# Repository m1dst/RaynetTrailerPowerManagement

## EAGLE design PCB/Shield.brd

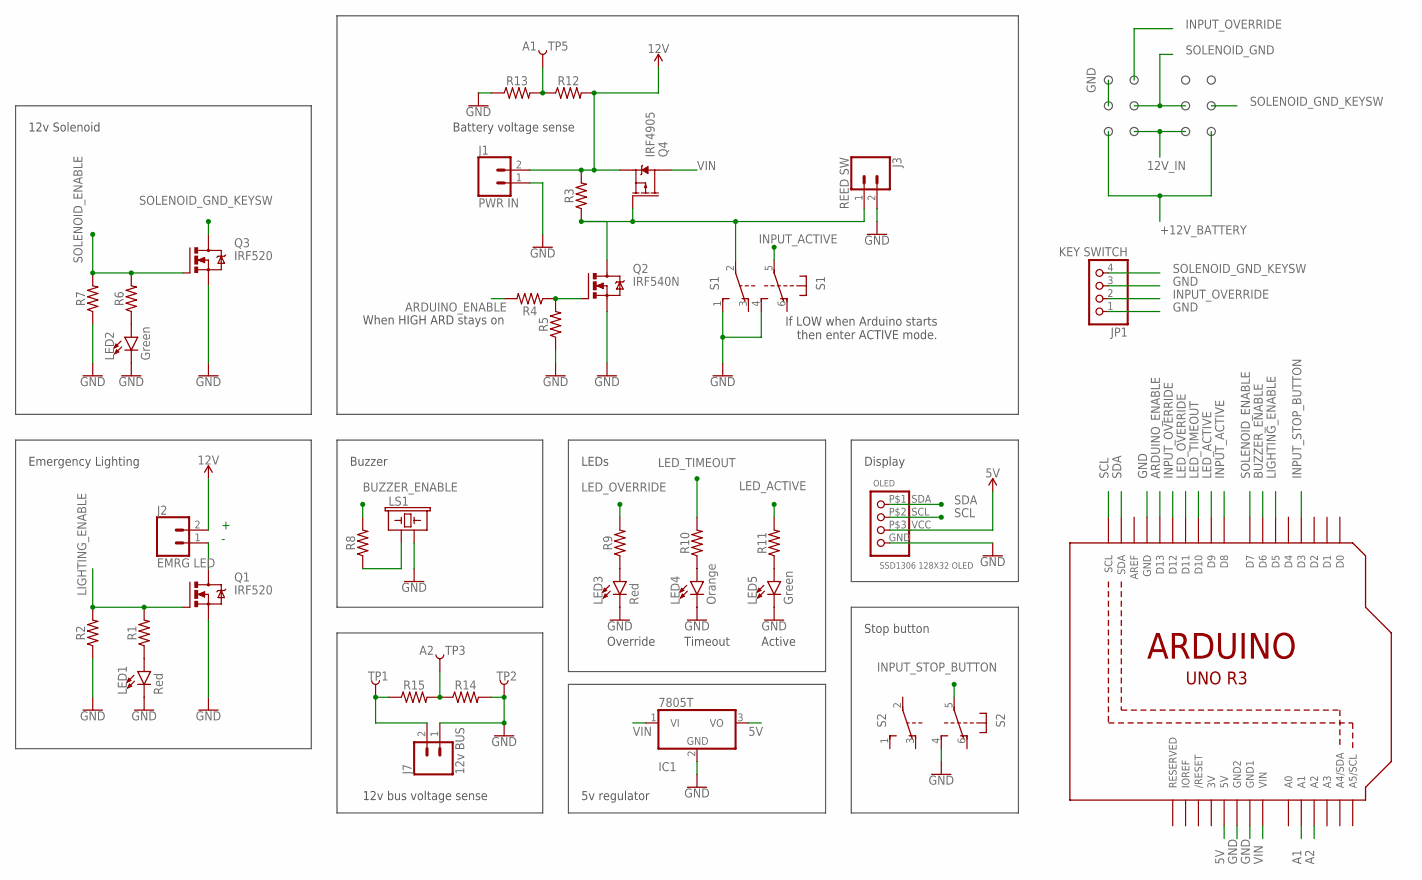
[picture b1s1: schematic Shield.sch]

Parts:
IC1: 7805T; TO220H
J1: PWR IN; SCREWTERMINAL-5MM-2
J2: EMRG LED; SCREWTERMINAL-5MM-2
J3: REED SW; SCREWTERMINAL-5MM-2
J7: 12v BUS; SCREWTERMINAL-5MM-2
JP1: KEY SWITCH; 1X04
LED1, LED3: Red; LED_3MM
LED2, LED5: Green; LED_3MM
LED4: Orange; LED_3MM
LS1: BUZZER; BUZZER-12MM-KIT
OLED: SSD1306 128X32 OLED; SSD1306_128X32_OLED
Q1, Q3: IRF520; TO220BV
Q2: IRF540N; TO220BV
Q4: IRF4905; TO220V
R1, R2, R6, R7: 1k; AXIAL-0.3
R3, R13, R14: 100k; AXIAL-0.3
R4, R8: 100; AXIAL-0.3
R5: 10k; AXIAL-0.3
R9, R10, R11: 330; AXIAL-0.3
R12, R15: 1m; AXIAL-0.3
S1, S2: 8X8_PCB_PUSH_BUTTON_DPDT
TP1, TP2, TP3, TP5: TEST-POINT3X5; PAD.03X.05
U1: ARDUINOR3-DIMENSION; ARDUINOR3

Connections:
3V: U1.3V
5V: IC1.3 (VO), OLED.P$3_VCC (VCC), U1.5V
12V_IN: J1.2, J2.2, Q4.3 (S), R3.P$2 (2), R12.P$2 (2)
A1: R12.P$1 (1), R13.P$2 (2), TP5.P$1, U1.A1
A2: R14.P$1 (1), R15.P$2 (2), TP3.P$1, U1.A2
ARDUINO_ENABLE: R4.P$2 (2), U1.D13
BUZZER_ENABLE: R8.P$2 (2), U1.D6
GND: IC1.2 (GND), J1.1, J3.2, J7.1, JP1.1, JP1.3, LED1.K (C), LED2.K (C), LED3.K (C), LED4.K (C), LED5.K (C), LS1.- (2), OLED.GND, Q1.S, Q2.S, Q3.S, R2.P$1 (1), R5.P$1 (1), R7.P$1 (1), R13.P$1 (1), R14.P$2 (2), S1.1 (S), S1.4 (S), S2.4 (S), TP2.P$1, U1.GND, U1.GND1, U1.GND2
INPUT_ACTIVE: S1.5, U1.D8
INPUT_OVERRIDE: JP1.2, U1.D12
INPUT_STOP_BUTTON: S2.5, U1.D3
LED_ACTIVE: R11.P$2 (2), U1.D9
LED_OVERRIDE: R9.P$2 (2), U1.D11
LED_TIMEOUT: R10.P$2 (2), U1.D10
LIGHTING_ENABLE: Q1.G, R1.P$2 (2), R2.P$2 (2), U1.D5
unnamed: J2.1, Q1.D
unnamed: LED1.A, R1.P$1 (1)
unnamed: J7.2, R15.P$1 (1), TP1.P$1
unnamed: J3.1, Q2.D, Q4.1 (G), R3.P$1 (1), S1.2
unnamed: Q2.G, R4.P$1 (1), R5.P$2 (2)
unnamed: LED2.A, R6.P$1 (1)
unnamed: LS1.+ (1), R8.P$1 (1)
unnamed: LED3.A, R9.P$1 (1)
unnamed: LED4.A, R10.P$1 (1)
unnamed: LED5.A, R11.P$1 (1)
SCL: OLED.P$2_SCL (SCL), U1.SCL
SDA: OLED.P$1_SDA (SDA), U1.SDA
SOLENOID_ENABLE: Q3.G, R6.P$2 (2), R7.P$2 (2), U1.D7
SOLENOID_GND_KEYSW: JP1.4, Q3.D
VIN: IC1.1 (VI), Q4.2 (D), U1.VIN

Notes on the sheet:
+ -
When HIGH ARD stays on
If LOW when Arduino starts then enter ACTIVE mode.
Emergency Lighting
12v Solenoid
Buzzer
Override
Timeout
Active
Battery voltage sense
12v bus voltage sense
LEDs
Display
Stop button
5v regulator

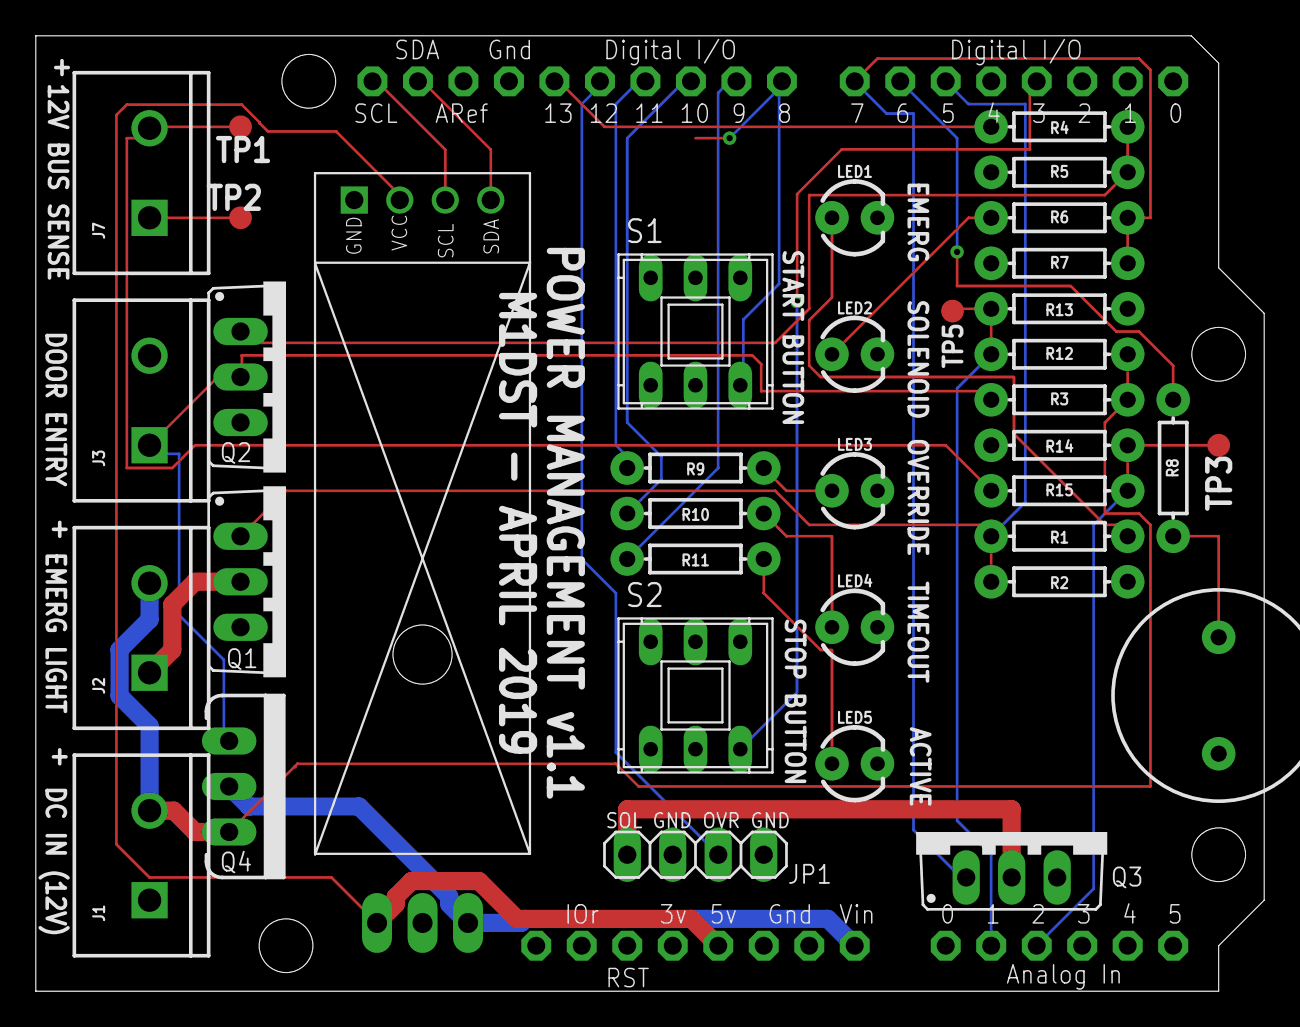
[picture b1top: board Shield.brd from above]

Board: 2 copper layers, 68.6 x 53.3 mm, 39 parts (1 on the bottom side), 29 nets.

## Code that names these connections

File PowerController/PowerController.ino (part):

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
#define SPARE               2     // Currently unused.
#define SOUND_BOMB          3     // The external burglar alarm
#define LIGHTING_ENABLE     4     // Emergency lighting.
#define SPARE_PWM           5     // Currently unused.
#define BUZZER_ENABLE       6     // The small buzzer.
#define SOLENOID_ENABLE     7     // The solenoid enable line.
#define INPUT_ACTIVE        8     // The start button
#define LED_ACTIVE          9     // Indicates if the Arduino power is now latched.
#define LED_TIMEOUT         10    // Indicates if the unit is in timeout mode and will eventually shutdown if no interaction occurs.
#define LED_OVERRIDE        11    // Indicates if override is active.
#define INPUT_OVERRIDE      12    // If grounded (via the keyswitch) the startup and under/over voltage checks are ignored.
#define ARDUINO_ENABLE      13    // Keeps the Arduino running.  If this pin goes low the Arduino will power off.

#define INPUT_ALARM_DISABLE A0    // Button to disable the alarm
#define INPUT_BATTERY_SENSE A1    // Measures the voltage of the battery.
#define INPUT_BUS_SENSE     A2    // Measures the voltage of the bus (controlled by the solenoid)
#define INPUT_STOP_BUTTON   A3    // The stop button.

#define BUZZER_SUPPORTED          // If uncommented, the buzzer will sound during events such as timeout.  Disabled during development.
#define DISPLAY_SUPPORTED         // If uncommented, the buzzer will sound during events such as timeout.  Disabled during development.
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  Serial.begin(115200);
  Serial.println("Starting...");

  pinMode(INPUT_STOP_BUTTON, INPUT);
  pinMode(INPUT_ACTIVE, INPUT_PULLUP);
  pinMode(INPUT_OVERRIDE, INPUT_PULLUP);

  pinMode(SOUND_BOMB, OUTPUT);      digitalWrite(SOUND_BOMB, LOW);
  pinMode(LIGHTING_ENABLE, OUTPUT); digitalWrite(LIGHTING_ENABLE, HIGH);
  pinMode(BUZZER_ENABLE, OUTPUT);   digitalWrite(BUZZER_ENABLE, LOW);
  pinMode(SOLENOID_ENABLE, OUTPUT); digitalWrite(SOLENOID_ENABLE, LOW);
  pinMode(ARDUINO_ENABLE, OUTPUT);  digitalWrite(ARDUINO_ENABLE, HIGH);
  pinMode(SPARE_PWM, OUTPUT);  digitalWrite(SPARE_PWM, LOW);

  pinMode(LED_ACTIVE, OUTPUT);    digitalWrite(LED_ACTIVE, LOW);
  pinMode(LED_TIMEOUT, OUTPUT);   digitalWrite(LED_TIMEOUT, LOW);
  pinMode(LED_OVERRIDE, OUTPUT);  digitalWrite(LED_OVERRIDE, LOW);

  // Setup the state machine transitions
  S0->addTransition(&transitionS0S1, S1);
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
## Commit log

2019-07-08 Version 1.0
    Core functionality - Requires cleanup and comments.
2020-08-17 Version 2.0
    Uses a state machine and interacts with a 3G GPS tracker.
2021-09-06 Allow the alarm to auto reset after 15 minutes.
2021-09-06 Attempt to fix some screen corruption
2021-09-13 Clean up

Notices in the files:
parts and their libraries:
SparkFun-LED: Licensing: Creative Commons ShareAlike 4.0 International - https://creativecommons.org/licenses/by-sa/4.0
